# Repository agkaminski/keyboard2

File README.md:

# keyboard2

This repository contains designs of mechanical keyboards. Purpose of these
keyboards are custom DIY computers that are of all-in-keyboard design.

## keyboard69

This is a DIY 69% (nice) mechanical keyboard. Mostly to be used for DIY
computers, but there's a provision for USB/PS2 connection too.

Keyboard has been tested in the [FellaPC](https://github.com/agkaminski/FellaPC)
project and proven 100% functional. USB/PS2 connection has not been tested yet.

### Photos

#### Top

#### Bottom

## keyboard_mini

This is a reduced version of keyboard69 - rightmost column has been removed,
PCB size is as small, as possible. Provision for USB/PS2 has been removed.
Other connectors remain compatible with keyboard69.

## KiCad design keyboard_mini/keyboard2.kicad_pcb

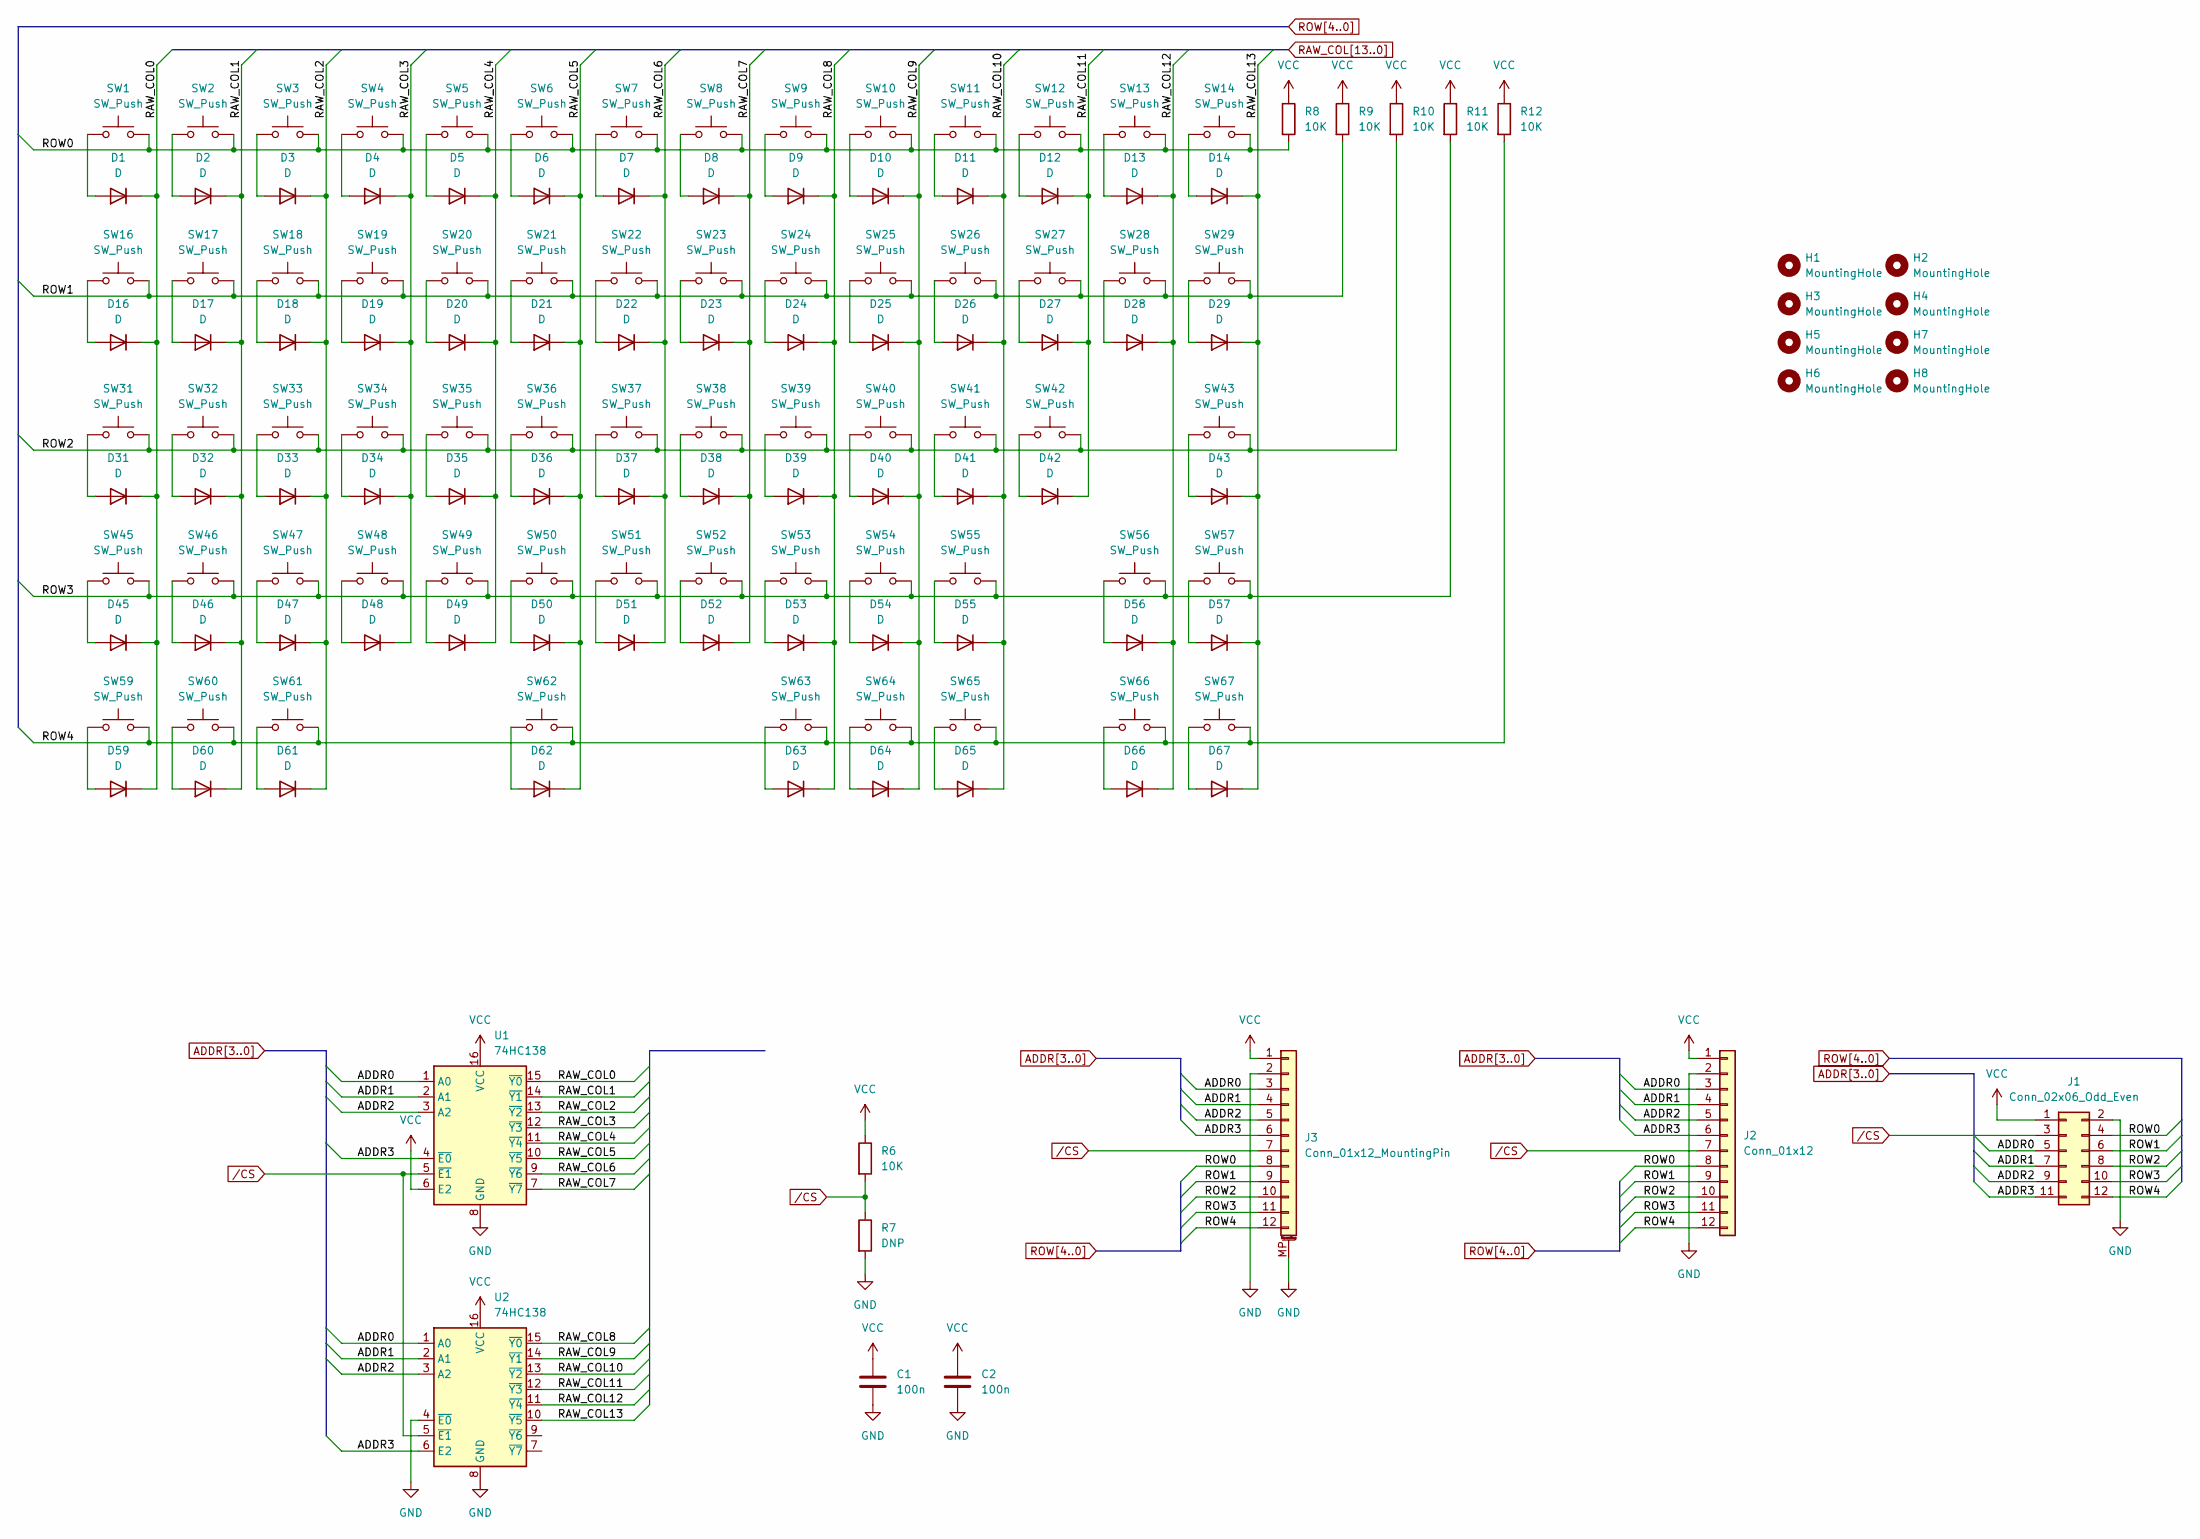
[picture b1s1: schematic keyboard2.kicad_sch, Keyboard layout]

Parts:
C1, C2: 100n; C_0805_2012Metric_Pad1.18x1.45mm_HandSolder
D1, D2, D3, D4, D5, D6, D7, D8, D9, D10, D11, D12, D13, D14, D16, D17, D18, D19, D20, D21, D22, D23, D24, D25, D26, D27, D28, D29, D31, D32, D33, D34, D35, D36, D37, D38, D39, D40, D41, D42, D43, D45, D46, D47, D48, D49, D50, D51, D52, D53, D54, D55, D56, D57, D59, D60, D61, D62, D63, D64, D65, D66, D67: D; D_MiniMELF
H1, H2, H3, H4, H5, H6, H7, H8: MountingHole; MountingHole_2.7mm_M2.5_Pad_Via
J1: Conn_02x06_Odd_Even; IDC-Header_2x06_P2.54mm_Vertical
J2: Conn_01x12; PinSocket_1x12_P2.54mm_Vertical
J3: Conn_01x12_MountingPin; TE_1-84952-2_1x12-1MP_P1.0mm_Horizontal
R6, R8, R9, R10, R11, R12: 10K; R_0805_2012Metric_Pad1.20x1.40mm_HandSolder
R7: DNP; R_0805_2012Metric_Pad1.20x1.40mm_HandSolder
SW1, SW2, SW3, SW4, SW5, SW6, SW7, SW8, SW9, SW10, SW11, SW12, SW13, SW17, SW18, SW19, SW20, SW21, SW22, SW23, SW24, SW25, SW26, SW27, SW28, SW32, SW33, SW34, SW35, SW36, SW37, SW38, SW39, SW40, SW41, SW42, SW46, SW47, SW48, SW49, SW50, SW51, SW52, SW53, SW54, SW55, SW57, SW63, SW64, SW65, SW66, SW67: SW_Push; SW_Cherry_MX_1.00u_PCB
SW14: SW_Push; SW_Cherry_MX_2.00u_PCB
SW16, SW29: SW_Push; SW_Cherry_MX_1.50u_PCB
SW31, SW56: SW_Push; SW_Cherry_MX_1.75u_PCB
SW43, SW45: SW_Push; SW_Cherry_MX_2.25u_PCB
SW59, SW60, SW61: SW_Push; SW_Cherry_MX_1.25u_PCB
SW62: SW_Push; SW_Cherry_MX_6.25u_PCB
U1, U2: 74HC138; SOIC-16_3.9x9.9mm_P1.27mm

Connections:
ADDR0: J1.5, J2.3, J3.3, U1.1 (A0), U2.1 (A0)
ADDR1: J1.7, J2.4, J3.4, U1.2 (A1), U2.2 (A1)
ADDR2: J1.9, J2.5, J3.5, U1.3 (A2), U2.3 (A2)
ADDR3: J1.11, J2.6, J3.6, U1.4 (~E0), U2.6 (E2)
GND: C1.2, C2.2, J1.2, J2.2, J3.2, J3.MP (MountPin), R7.2, U1.8 (GND), U2.4 (~E0), U2.8 (GND)
unnamed: D1.2 (A), SW1.1
unnamed: D2.2 (A), SW2.1
unnamed: D3.2 (A), SW3.1
unnamed: D4.2 (A), SW4.1
unnamed: D5.2 (A), SW5.1
unnamed: D6.2 (A), SW6.1
unnamed: D7.2 (A), SW7.1
unnamed: D8.2 (A), SW8.1
unnamed: D9.2 (A), SW9.1
unnamed: D10.2 (A), SW10.1
unnamed: D11.2 (A), SW11.1
unnamed: D12.2 (A), SW12.1
unnamed: D13.2 (A), SW13.1
unnamed: D14.2 (A), SW14.1
unnamed: D16.2 (A), SW16.1
unnamed: D17.2 (A), SW17.1
unnamed: D18.2 (A), SW18.1
unnamed: D19.2 (A), SW19.1
unnamed: D20.2 (A), SW20.1
unnamed: D21.2 (A), SW21.1
unnamed: D22.2 (A), SW22.1
unnamed: D23.2 (A), SW23.1
unnamed: D24.2 (A), SW24.1
unnamed: D25.2 (A), SW25.1
unnamed: D26.2 (A), SW26.1
unnamed: D27.2 (A), SW27.1
unnamed: D28.2 (A), SW28.1
unnamed: D29.2 (A), SW29.1
unnamed: D31.2 (A), SW31.1
unnamed: D32.2 (A), SW32.1
unnamed: D33.2 (A), SW33.1
unnamed: D34.2 (A), SW34.1
unnamed: D35.2 (A), SW35.1
unnamed: D36.2 (A), SW36.1
unnamed: D37.2 (A), SW37.1
unnamed: D38.2 (A), SW38.1
unnamed: D39.2 (A), SW39.1
unnamed: D40.2 (A), SW40.1
unnamed: D41.2 (A), SW41.1
unnamed: D42.2 (A), SW42.1
unnamed: D43.2 (A), SW43.1
unnamed: D45.2 (A), SW45.1
unnamed: D46.2 (A), SW46.1
unnamed: D47.2 (A), SW47.1
unnamed: D48.2 (A), SW48.1
unnamed: D49.2 (A), SW49.1
unnamed: D50.2 (A), SW50.1
unnamed: D51.2 (A), SW51.1
unnamed: D52.2 (A), SW52.1
unnamed: D53.2 (A), SW53.1
unnamed: D54.2 (A), SW54.1
unnamed: D55.2 (A), SW55.1
unnamed: D56.2 (A), SW56.1
unnamed: D57.2 (A), SW57.1
unnamed: D59.2 (A), SW59.1
unnamed: D60.2 (A), SW60.1
unnamed: D61.2 (A), SW61.1
unnamed: D62.2 (A), SW62.1
unnamed: D63.2 (A), SW63.1
unnamed: D64.2 (A), SW64.1
unnamed: D65.2 (A), SW65.1
unnamed: D66.2 (A), SW66.1
unnamed: D67.2 (A), SW67.1
RAW_COL0: D1.1 (K), D16.1 (K), D31.1 (K), D45.1 (K), D59.1 (K), U1.15 (~Y0)
RAW_COL1: D2.1 (K), D17.1 (K), D32.1 (K), D46.1 (K), D60.1 (K), U1.14 (~Y1)
RAW_COL2: D3.1 (K), D18.1 (K), D33.1 (K), D47.1 (K), D61.1 (K), U1.13 (~Y2)
RAW_COL3: D4.1 (K), D19.1 (K), D34.1 (K), D48.1 (K), U1.12 (~Y3)
RAW_COL4: D5.1 (K), D20.1 (K), D35.1 (K), D49.1 (K), U1.11 (~Y4)
RAW_COL5: D6.1 (K), D21.1 (K), D36.1 (K), D50.1 (K), D62.1 (K), U1.10 (~Y5)
RAW_COL6: D7.1 (K), D22.1 (K), D37.1 (K), D51.1 (K), U1.9 (~Y6)
RAW_COL7: D8.1 (K), D23.1 (K), D38.1 (K), D52.1 (K), U1.7 (~Y7)
RAW_COL8: D9.1 (K), D24.1 (K), D39.1 (K), D53.1 (K), D63.1 (K), U2.15 (~Y0)
RAW_COL9: D10.1 (K), D25.1 (K), D40.1 (K), D54.1 (K), D64.1 (K), U2.14 (~Y1)
RAW_COL10: D11.1 (K), D26.1 (K), D41.1 (K), D55.1 (K), D65.1 (K), U2.13 (~Y2)
RAW_COL11: D12.1 (K), D27.1 (K), D42.1 (K), U2.12 (~Y3)
RAW_COL12: D13.1 (K), D28.1 (K), D56.1 (K), D66.1 (K), U2.11 (~Y4)
RAW_COL13: D14.1 (K), D29.1 (K), D43.1 (K), D57.1 (K), D67.1 (K), U2.10 (~Y5)
ROW0: J1.4, J2.8, J3.8, R8.2, SW1.2, SW2.2, SW3.2, SW4.2, SW5.2, SW6.2, SW7.2, SW8.2, SW9.2, SW10.2, SW11.2, SW12.2, SW13.2, SW14.2
ROW1: J1.6, J2.9, J3.9, R9.2, SW16.2, SW17.2, SW18.2, SW19.2, SW20.2, SW21.2, SW22.2, SW23.2, SW24.2, SW25.2, SW26.2, SW27.2, SW28.2, SW29.2
ROW2: J1.8, J2.10, J3.10, R10.2, SW31.2, SW32.2, SW33.2, SW34.2, SW35.2, SW36.2, SW37.2, SW38.2, SW39.2, SW40.2, SW41.2, SW42.2, SW43.2
ROW3: J1.10, J2.11, J3.11, R11.2, SW45.2, SW46.2, SW47.2, SW48.2, SW49.2, SW50.2, SW51.2, SW52.2, SW53.2, SW54.2, SW55.2, SW56.2, SW57.2
ROW4: J1.12, J2.12, J3.12, R12.2, SW59.2, SW60.2, SW61.2, SW62.2, SW63.2, SW64.2, SW65.2, SW66.2, SW67.2
VCC: C1.1, C2.1, J1.1, J2.1, J3.1, R6.1, R8.1, R9.1, R10.1, R11.1, R12.1, U1.6 (E2), U1.16 (VCC), U2.16 (VCC)
/CS: J1.3, J2.7, J3.7, R6.2, R7.1, U1.5 (~E1), U2.5 (~E1)

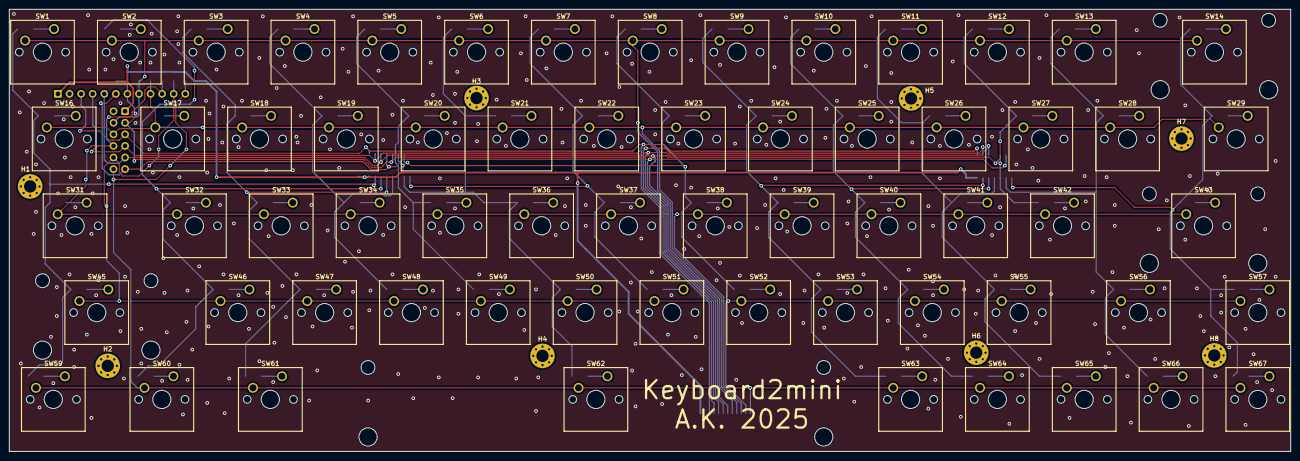
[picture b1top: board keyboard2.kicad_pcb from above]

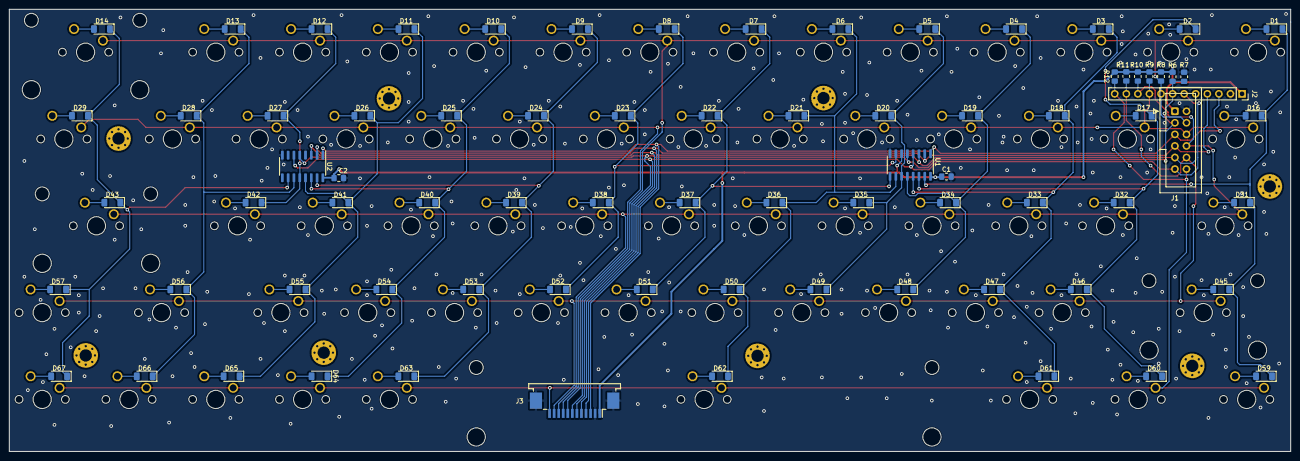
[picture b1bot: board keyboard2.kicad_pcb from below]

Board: 2 copper layers, 281.2 x 97.0 mm, 148 parts (77 on the bottom side), 89 nets.

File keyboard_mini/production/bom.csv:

Designator,Footprint,Quantity,Value,LCSC Part #
"C1, C2",0805,2,100n,
"D1, D10, D11, D12, D13, D14, D16, D17, D18, D19, D2, D20, D21, D22, D23, D24, D25, D26, D27, D28, D29, D3, D31, D32, D33, D34, D35, D36, D37, D38, D39, D4, D40, D41, D42, D43, D45, D46, D47, D48, D49, D5, D50, D51, D52, D53, D54, D55, D56, D57, D59, D6, D60, D61, D62, D63, D64, D65, D66, D67, D7, D8, D9",D_MiniMELF,63,D,
J1,IDC-Header_2x06_P2.54mm_Vertical,1,Conn_02x06_Odd_Even,
J2,PinSocket_1x12_P2.54mm_Vertical,1,Conn_01x12,
J3,TE_1-84952-2_1x12-1MP_P1.0mm_Horizontal,1,Conn_01x12_MountingPin,
"R10, R11, R12, R6, R8, R9",0805,6,10K,
R7,0805,1,DNP,
"SW1, SW10, SW11, SW12, SW13, SW17, SW18, SW19, SW2, SW20, SW21, SW22, SW23, SW24, SW25, SW26, SW27, SW28, SW3, SW32, SW33, SW34, SW35, SW36, SW37, SW38, SW39, SW4, SW40, SW41, SW42, SW46, SW47, SW48, SW49, SW5, SW50, SW51, SW52, SW53, SW54, SW55, SW57, SW6, SW63, SW64, SW65, SW66, SW67, SW7, SW8, SW9",SW_Cherry_MX_1.00u_PCB,52,SW_Push,
SW14,SW_Cherry_MX_2.00u_PCB,1,SW_Push,
"SW16, SW29",SW_Cherry_MX_1.50u_PCB,2,SW_Push,
"SW31, SW56",SW_Cherry_MX_1.75u_PCB,2,SW_Push,
"SW43, SW45",SW_Cherry_MX_2.25u_PCB,2,SW_Push,
"SW59, SW60, SW61",SW_Cherry_MX_1.25u_PCB,3,SW_Push,
SW62,SW_Cherry_MX_6.25u_PCB,1,SW_Push,
"U1, U2",SOIC-16_3.9x9.9mm_P1.27mm,2,74HC138,

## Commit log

2024-03-17 Initial import
2024-03-17 Add AVR WIP code
2024-03-17 Add photos
2024-03-22 Revision B:
    - fix wrong space size (6.5u -> 6.25u),
    - fix wrong right shift size (2u -> 1.75u),
    - fix wrong placement of space stabilizer,
    - fix J1 being mirrored against IDC-12 connector,
    - change diodes footprint (hand soldering version has way too big pads),
    - reroute.
2025-04-22 Add mechanical drawing and step model
2025-05-04 Add mini version
2025-05-05 Repo cleanup
2025-05-05 Add keyboard2 mini
2025-05-05 Add gitignore
2025-05-05 mini: add step model
